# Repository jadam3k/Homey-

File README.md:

# Homey

Homey is a compact home automation controller designed for residential use, while also being capable of operating as an industrial-style PLC for control and monitoring tasks.

The project combines Ethernet connectivity, isolated digital I/O, relay outputs, and flexible power input in a single hardware platform built around ESP32.

---

## Hardware Features

* **ESP32-based architecture** for wireless communication, local control logic, and future expansion.
* **Ethernet with PoE support** for reliable wired connectivity and simplified installation.
* **4 digital inputs** for external sensors, switches, and automation signals.
* **4 digital outputs** based on relays for switching external loads.
* **5 onboard LEDs** used for status indication, diagnostics, and visual feedback.
* **Input voltage up to 24V** for industrial and field applications.
* **5V relay section** powered separately while maintaining compatibility with higher external voltages.
* **USB-C power support** for development, testing, and low-voltage standalone operation.
* **Optocoupler isolation** allowing safe interfacing with higher voltage external circuits.

---

## Electrical Design Notes

The board is divided into functional sections.

High-voltage and switching circuitry are separated from the low-voltage logic domain in order to improve stability, reduce electrical noise, and increase operational safety.

Special attention was given to routing of high-speed and differential signals such as:

* Ethernet TX / RX
* USB D+ / D−

Component placement and routing were performed with signal integrity and practical manufacturability in mind.

---

## Firmware

The firmware has been completed and provides the basic control layer for the board.

The current software handles:

* digital input reading
* relay output control
* status LED logic
* Ethernet communication foundation

The architecture was kept clean and modular to allow future expansion for everyone - you do what you want :).

A future direction of development is communication between multiple boards using **ESP-NOW**, enabling distributed control nodes over larger areas (2/3km).

---

## Project Images

### 3D Model

### Schematic

### PCB Layout / Routed Board

---

## Project Status

The project is currently considered **complete**.

Remember, if you copy it. Mention me :) i will check that.

---

## License
Just do not consider this project as your own :)

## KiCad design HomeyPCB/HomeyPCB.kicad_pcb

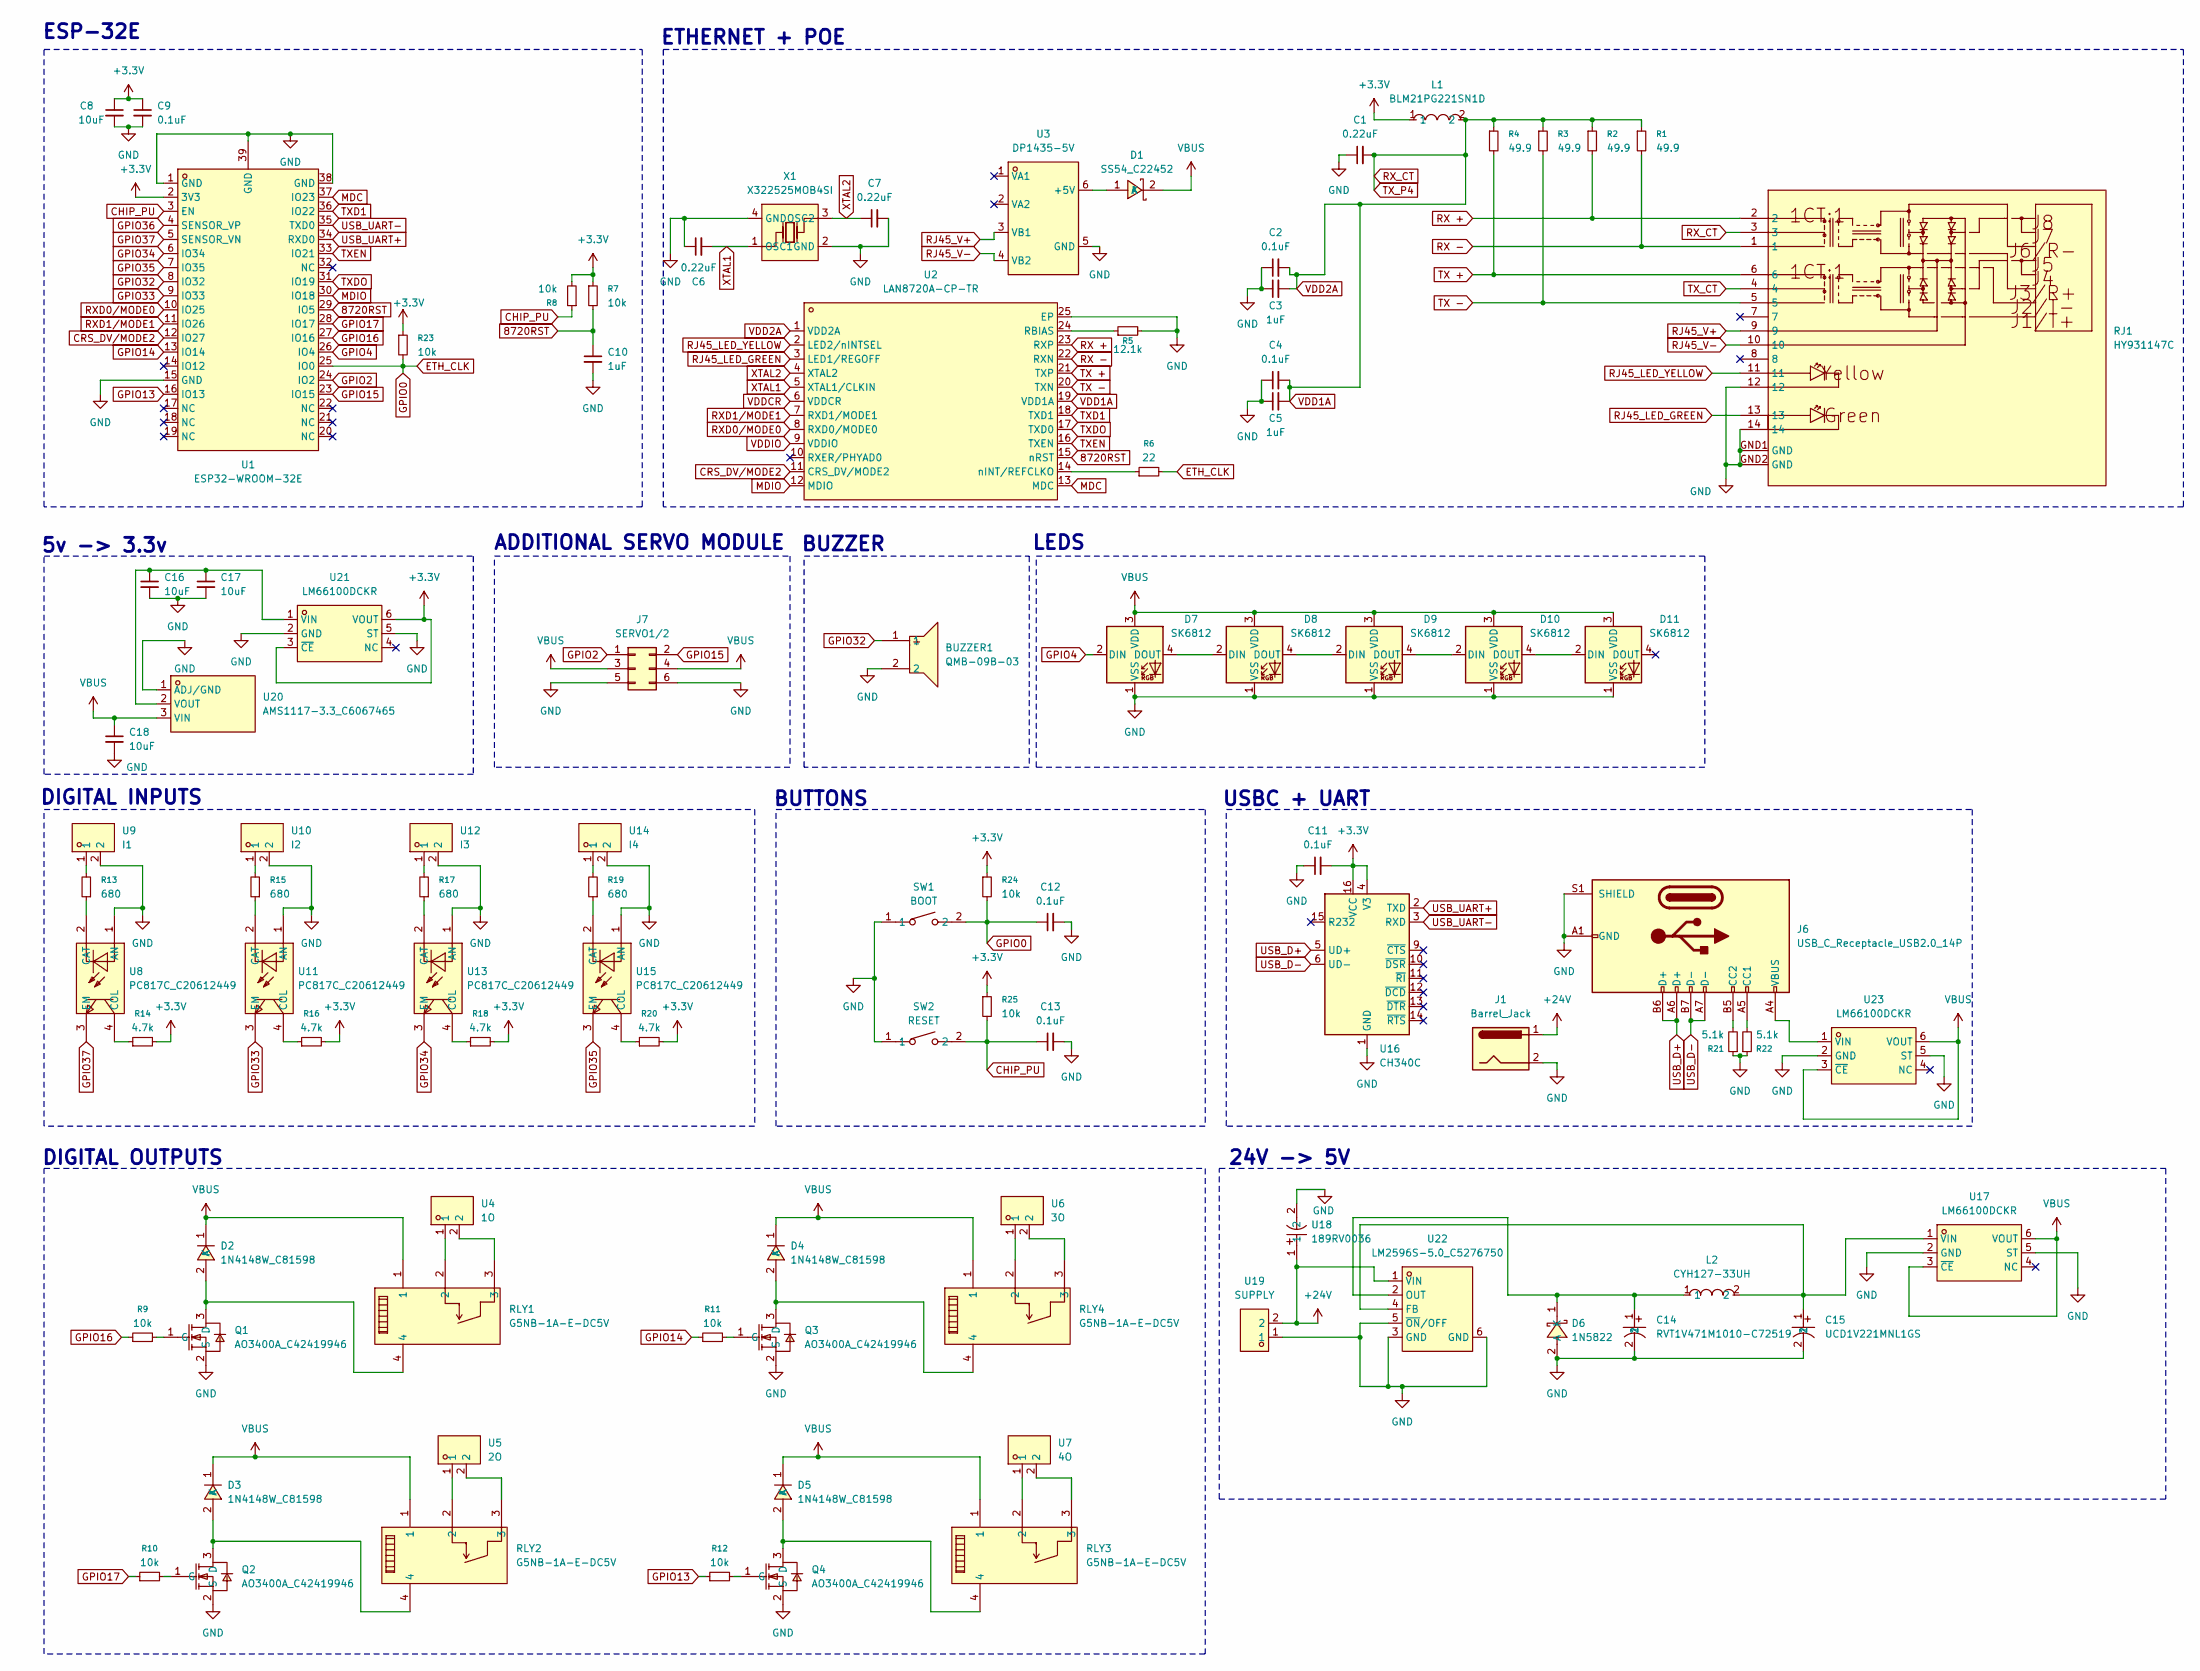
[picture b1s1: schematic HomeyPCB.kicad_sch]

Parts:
BUZZER1: QMB-09B-03; BUZ-TH_BD9.0-P4.00-D0.6-FD; MPN QMB-09B-03; LCSC Part C96256
C1, C6, C7: 0.22uF; C_0603_1608Metric_Pad1.08x0.95mm_HandSolder
C2, C4, C9, C11, C12, C13: 0.1uF; C_0603_1608Metric_Pad1.08x0.95mm_HandSolder
C3, C5, C10: 1uF; C_0603_1608Metric_Pad1.08x0.95mm_HandSolder
C8, C16, C17, C18: 10uF; C_0603_1608Metric_Pad1.08x0.95mm_HandSolder
C14: RVT1V471M1010-C72519; CAP-SMD_BD10.0-L10.3-W10.3-LS11.0-R-RD; MPN RVT1V471M1010; LCSC Part C72519
C15: UCD1V221MNL1GS; CAP-SMD_BD8.0-L8.3-W8.3-LS9.3-FD-2; MPN UCD1V221MNL1GS; LCSC Part C136294
D1: SS54_C22452; SMA_L4.4-W2.8-LS5.4-R-RD; MPN SS54; LCSC Part C22452
D2, D3, D4, D5: 1N4148W_C81598; SOD-123F_L2.7-W1.6-LS3.8-RD; MPN 1N4148W; LCSC Part C81598
D6: 1N5822; DO-201AD_BD5.3-L8.4-P12.50-D1.4-RD; MPN 1N5822; LCSC Part C47345510
D7, D8, D9, D10, D11: SK6812; LED_SK6812_PLCC4_5.0x5.0mm_P3.2mm
J1: Barrel_Jack; BarrelJack_Horizontal
J6: USB_C_Receptacle_USB2.0_14P; USB_C_Receptacle_HRO_TYPE-C-31-M-12
J7: SERVO1/2; PinHeader_2x03_P2.54mm_Vertical
L1: BLM21PG221SN1D; L0805; MPN BLM21PG221SN1D; LCSC Part C85840
L2: CYH127-33UH; IND-SMD_L12.3-W12.3; MPN CYH127-33UH; LCSC Part C2929502
Q1, Q2, Q3, Q4: AO3400A_C42419946; SOT-23-3_L2.9-W1.3-P1.90-LS2.4-BR; MPN AO3400A; LCSC Part C42419946
R1, R2, R3, R4: 49.9; R_0603_1608Metric_Pad0.98x0.95mm_HandSolder
R5: 12.1k; R_0603_1608Metric_Pad0.98x0.95mm_HandSolder
R6: 22; R_0603_1608Metric_Pad0.98x0.95mm_HandSolder
R7, R8, R9, R10, R11, R12, R23, R24, R25: 10k; R_0603_1608Metric_Pad0.98x0.95mm_HandSolder
R13, R15, R17, R19: 680; R_2512_6332Metric_Pad1.40x3.35mm_HandSolder
R14, R16, R18, R20: 4.7k; R_0603_1608Metric_Pad0.98x0.95mm_HandSolder
R21, R22: 5.1k; R_0603_1608Metric_Pad0.98x0.95mm_HandSolder
RJ1: HY931147C; RJ45-TH_HY931147C; MPN HY931147C; LCSC Part C91754
RLY1, RLY2, RLY3, RLY4: G5NB-1A-E-DC5V; RELAY-TH_G5NB-1A-E-DCXX; MPN G5NB-1A-E-DC5V; LCSC Part C48746
SW1: BOOT; SW-SMD_L3.9-W3.0-P4.45; MPN TS-1088-AR02016; LCSC Part C720477
SW2: RESET; SW-SMD_L3.9-W3.0-P4.45; MPN TS-1088-AR02016; LCSC Part C720477
U1: ESP32-WROOM-32E; WIFI-SMD_ESP32-WROOM-32E; MPN ESP32-WROOM-32E-N8; LCSC Part C701342
U2: LAN8720A-CP-TR; QFN-24_L4.0-W4.0-P0.50-BL-EP2.6; MPN LAN8720A-CP-TR; LCSC Part C45223
U3: DP1435-5V; PWRM-TH_L35.6-W16.2-P2.54_DP1435-5V; MPN DP1435-5V; LCSC Part C5380097
U4: 1O; CONN-TH_P5.00_KF301-5.0-2P; MPN KF301-5.0-2P; LCSC Part C474881
U5: 2O; CONN-TH_P5.00_KF301-5.0-2P; MPN KF301-5.0-2P; LCSC Part C474881
U6: 3O; CONN-TH_P5.00_KF301-5.0-2P; MPN KF301-5.0-2P; LCSC Part C474881
U7: 4O; CONN-TH_P5.00_KF301-5.0-2P; MPN KF301-5.0-2P; LCSC Part C474881
U8, U11, U13, U15: PC817C_C20612449; DIP-4_L4.6-W6.5-P2.54-LS7.6-BL; MPN PC817C; LCSC Part C20612449
U9: I1; CONN-TH_P5.00_KF301-5.0-2P; MPN KF301-5.0-2P; LCSC Part C474881
U10: I2; CONN-TH_P5.00_KF301-5.0-2P; MPN KF301-5.0-2P; LCSC Part C474881
U12: I3; CONN-TH_P5.00_KF301-5.0-2P; MPN KF301-5.0-2P; LCSC Part C474881
U14: I4; CONN-TH_P5.00_KF301-5.0-2P; MPN KF301-5.0-2P; LCSC Part C474881
U16: CH340C; SOIC-16_3.9x9.9mm_P1.27mm
U17, U21, U23: LM66100DCKR; SC-70-6_L2.0-W1.3-P0.65-LS2.1-BL; MPN LM66100DCKR; LCSC Part C2869734
U18: 189RV0036; CAP-SMD_BD10.0-L10.3-W10.3-LS10.8-FD; MPN 189RV0036; LCSC Part C7471898
U19: SUPPLY; CONN-TH_P5.00_KF301-5.0-2P; MPN KF301-5.0-2P; LCSC Part C474881
U20: AMS1117-3.3_C6067465; SOT-89-3_L4.5-W2.5-P1.50-LS4.2-BR; MPN AMS1117-3.3; LCSC Part C6067465
U22: LM2596S-5.0_C5276750; TO-263-5_L10.1-W8.7-P1.70-LS15.2-BR; MPN LM2596S-5.0; LCSC Part C5276750
X1: X322525MOB4SI; CRYSTAL-SMD_4P-L3.2-W2.5-BL; MPN X322525MOB4SI; LCSC Part C9006

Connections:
8720RST: C10.1, R7.2, U1.29 (IO5), U2.15 (nRST)
+3.3V: C8.1, C9.1, C11.2, L1.1, R7.1, R8.2, R14.2, R16.2, R18.2, R20.2, R23.1, R24.1, R25.1, U1.2 (3V3), U16.4 (V3), U16.16 (VCC), U21.3 (~CE), U21.6 (VOUT)
+24V: J1.1, U18.1, U19.2, U22.1 (VIN)
CHIP_PU: C13.1, R8.1, R25.2, SW2.2, U1.3 (EN)
CRS_DV/MODE2: U1.12 (IO27), U2.11 (CRS_DV/MODE2)
ETH_CLK: C12.1, R6.2, R23.2, R24.2, SW1.2, U1.25 (IO0)
GND: BUZZER1.2, C1.1, C2.1, C3.1, C4.1, C5.1, C6.1, C7.2, C8.2, C9.2, C10.2, C11.1, C12.2, C13.2, C14.2, C15.2, C16.2, C17.2, C18.2, D6.2 (A), D7.1 (VSS), D8.1 (VSS), D9.1 (VSS), D10.1 (VSS), D11.1 (VSS), J1.2, J6.A1 (GND), J6.A12 (GND), J6.B1 (GND), J6.B12 (GND), J6.S1 (SHIELD), J7.5, J7.6, Q1.2 (S), Q2.2 (S), Q3.2 (S), Q4.2 (S), R5.2, R21.1, R22.1, RJ1.12, RJ1.14, RJ1.GND1 (GND), RJ1.GND2 (GND), SW1.1, SW2.1, U1.1 (GND), U1.15 (GND), U1.38 (GND), U1.39 (GND), U2.25 (EP), U3.5 (GND), U8.1 (AN), U9.2, U10.2, U11.1 (AN), U12.2, U13.1 (AN), U14.2, U15.1 (AN), U16.1 (GND), U17.2 (GND), U17.5 (ST), U18.2, U19.1, U20.1 (ADJ/GND), U21.2 (GND), U21.5 (ST), U22.3 (GND), U22.5 (~ON/OFF), U22.6 (GND), U23.2 (GND), U23.5 (ST), X1.2 (GND), X1.4 (GND)
GPIO2: J7.1, U1.24 (IO2)
GPIO4: D7.2 (DIN), U1.26 (IO4)
GPIO13: R12.1, U1.16 (IO13)
GPIO14: R11.1, U1.13 (IO14)
GPIO15: J7.2, U1.23 (IO15)
GPIO16: R9.1, U1.27 (IO16)
GPIO17: R10.1, U1.28 (IO17)
GPIO32: BUZZER1.1, U1.8 (IO32)
GPIO33: U1.9 (IO33), U11.3 (EM)
GPIO34: U1.6 (IO34), U13.3 (EM)
GPIO35: U1.7 (IO35), U15.3 (EM)
GPIO36: U1.4 (SENSOR_VP)
GPIO37: U1.5 (SENSOR_VN), U8.3 (EM)
MDC: U1.37 (IO23), U2.13 (MDC)
MDIO: U1.30 (IO18), U2.12 (MDIO)
unnamed: D1.1 (A), U3.6 (+5V)
unnamed: D2.2 (A), Q1.3 (D), RLY1.4
unnamed: D3.2 (A), Q2.3 (D), RLY2.4
unnamed: D4.2 (A), Q3.3 (D), RLY4.4
unnamed: D5.2 (A), Q4.3 (D), RLY3.4
unnamed: C14.1, D6.1 (K), L2.1, U22.2 (OUT)
unnamed: D7.4 (DOUT), D8.2 (DIN)
unnamed: D8.4 (DOUT), D9.2 (DIN)
unnamed: D9.4 (DOUT), D10.2 (DIN)
unnamed: D10.4 (DOUT), D11.2 (DIN)
unnamed: J6.A5 (CC1), R22.2
unnamed: J6.B5 (CC2), R21.2
unnamed: Q1.1 (G), R9.2
unnamed: Q2.1 (G), R10.2
unnamed: Q3.1 (G), R11.2
unnamed: Q4.1 (G), R12.2
unnamed: R13.2, U9.1
unnamed: R15.2, U10.1
unnamed: R17.2, U12.1
unnamed: R19.2, U14.1
unnamed: RLY1.2, U4.1
unnamed: RLY1.3, U4.2
unnamed: RLY2.2, U5.1
unnamed: RLY2.3, U5.2
unnamed: RLY3.2, U7.1
unnamed: RLY3.3, U7.2
unnamed: RLY4.2, U6.1
unnamed: RLY4.3, U6.2
unnamed: R5.1, U2.24 (RBIAS)
unnamed: R6.1, U2.14 (nINT/REFCLKO)
unnamed: R13.1, U8.2 (CAT)
unnamed: R14.1, U8.4 (COL)
unnamed: R15.1, U11.2 (CAT)
unnamed: R16.1, U11.4 (COL)
unnamed: R17.1, U13.2 (CAT)
unnamed: R18.1, U13.4 (COL)
unnamed: R19.1, U15.2 (CAT)
unnamed: R20.1, U15.4 (COL)
unnamed: C15.1, L2.2, U17.1 (VIN), U22.4 (FB)
unnamed: C16.1, C17.1, U20.2 (VOUT), U21.1 (VIN)
unnamed: J6.A4 (VBUS), J6.A9 (VBUS), J6.B4 (VBUS), J6.B9 (VBUS), U23.1 (VIN)
RJ45_LED_GREEN: RJ1.13, U2.3 (LED1/REGOFF)
RJ45_LED_YELLOW: RJ1.11, U2.2 (LED2/nINTSEL)
RJ45_V+: RJ1.9, U3.3 (VB1)
RJ45_V-: RJ1.10, U3.4 (VB2)
RX +: R2.2, RJ1.2, U2.23 (RXP)
RX -: R1.2, RJ1.1, U2.22 (RXN)
RXD0/MODE0: U1.10 (IO25), U2.8 (RXD0/MODE0)
RXD1/MODE1: U1.11 (IO26), U2.7 (RXD1/MODE1)
RX_CT: C1.2, C2.2, C3.2, C4.2, C5.2, L1.2, R1.1, R2.1, R3.1, R4.1, RJ1.3, U2.1 (VDD2A), U2.19 (VDD1A)
TX +: R4.2, RJ1.6, U2.21 (TXP)
TX -: R3.2, RJ1.5, U2.20 (TXN)
TXD1: U1.36 (IO22), U2.18 (TXD1)
TXDO: U1.31 (IO19), U2.17 (TXD0)
TXEN: U1.33 (IO21), U2.16 (TXEN)
TX_CT: RJ1.4
USB_D+: J6.A6 (D+), J6.B6 (D+), U16.5 (UD+)
USB_D-: J6.A7 (D-), J6.B7 (D-), U16.6 (UD-)
USB_UART+: U1.34 (RXD0), U16.2 (TXD)
USB_UART-: U1.35 (TXD0), U16.3 (RXD)
VBUS: C18.1, D1.2 (K), D2.1 (K), D3.1 (K), D4.1 (K), D5.1 (K), D7.3 (VDD), D8.3 (VDD), D9.3 (VDD), D10.3 (VDD), D11.3 (VDD), J7.3, J7.4, RLY1.1, RLY2.1, RLY3.1, RLY4.1, U17.3 (~CE), U17.6 (VOUT), U20.3 (VIN), U23.3 (~CE), U23.6 (VOUT)
VDDCR: U2.6 (VDDCR)
VDDIO: U2.9 (VDDIO)
XTAL1: C6.2, U2.5 (XTAL1/CLKIN), X1.1 (OSC1)
XTAL2: C7.1, U2.4 (XTAL2), X1.3 (OSC2)

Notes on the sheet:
ESP-32E
USBC + UART
ETHERNET + POE
5v -> 3.3v
BUTTONS
LEDS
DIGITAL INPUTS
BUZZER
ADDITIONAL SERVO MODULE
24V -> 5V
DIGITAL OUTPUTS

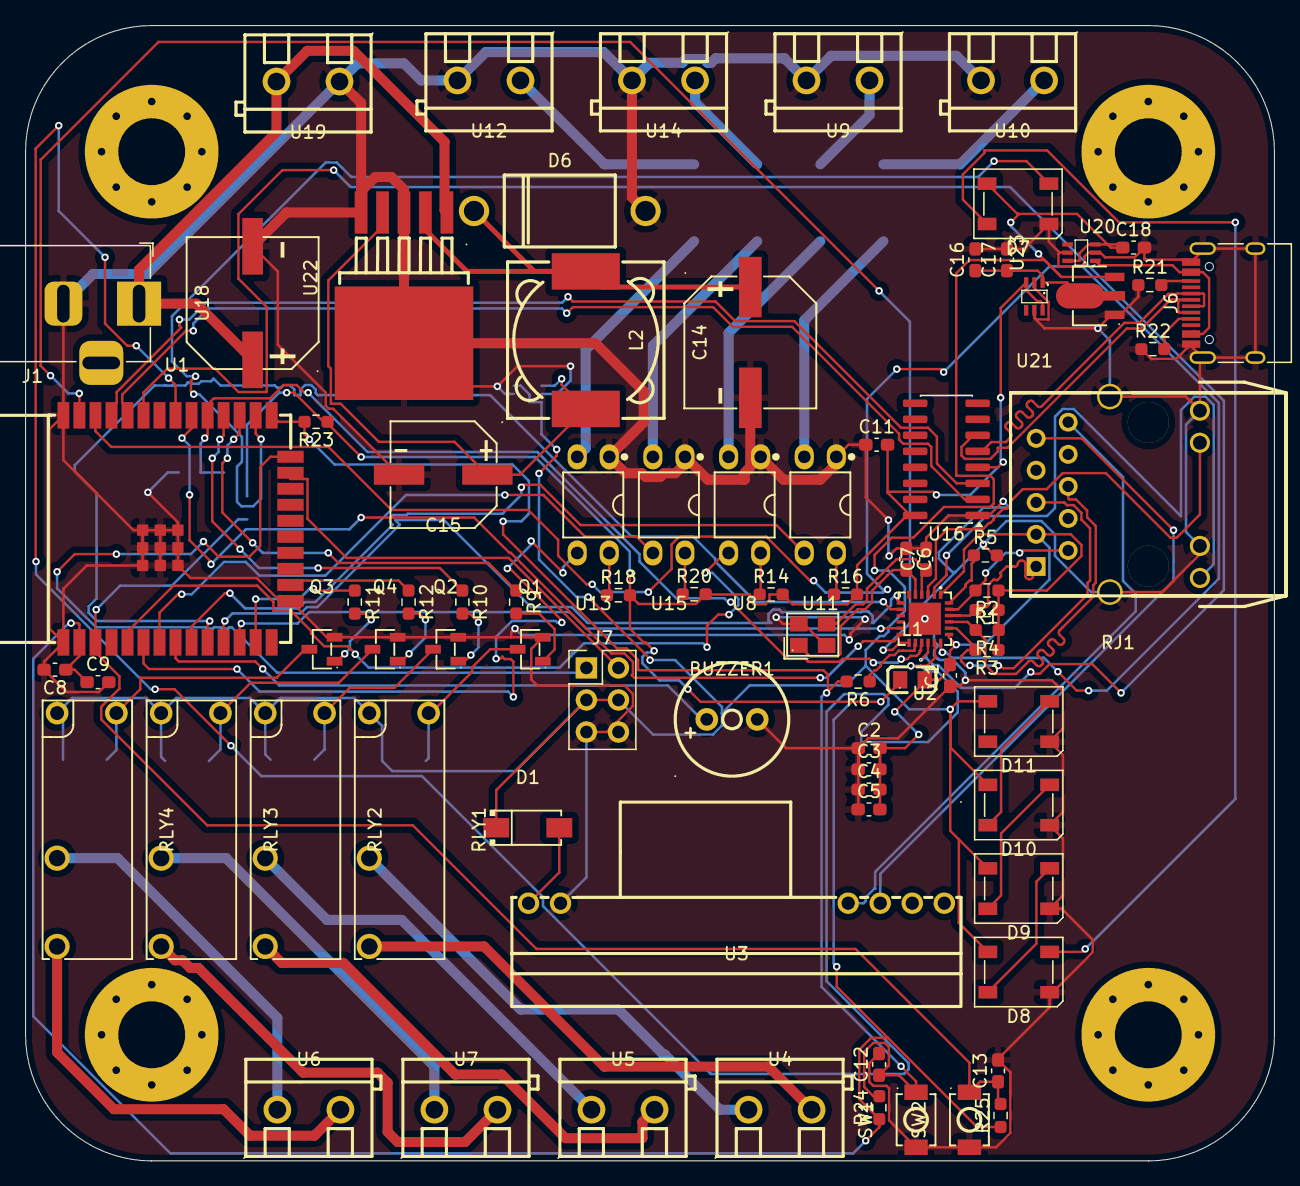
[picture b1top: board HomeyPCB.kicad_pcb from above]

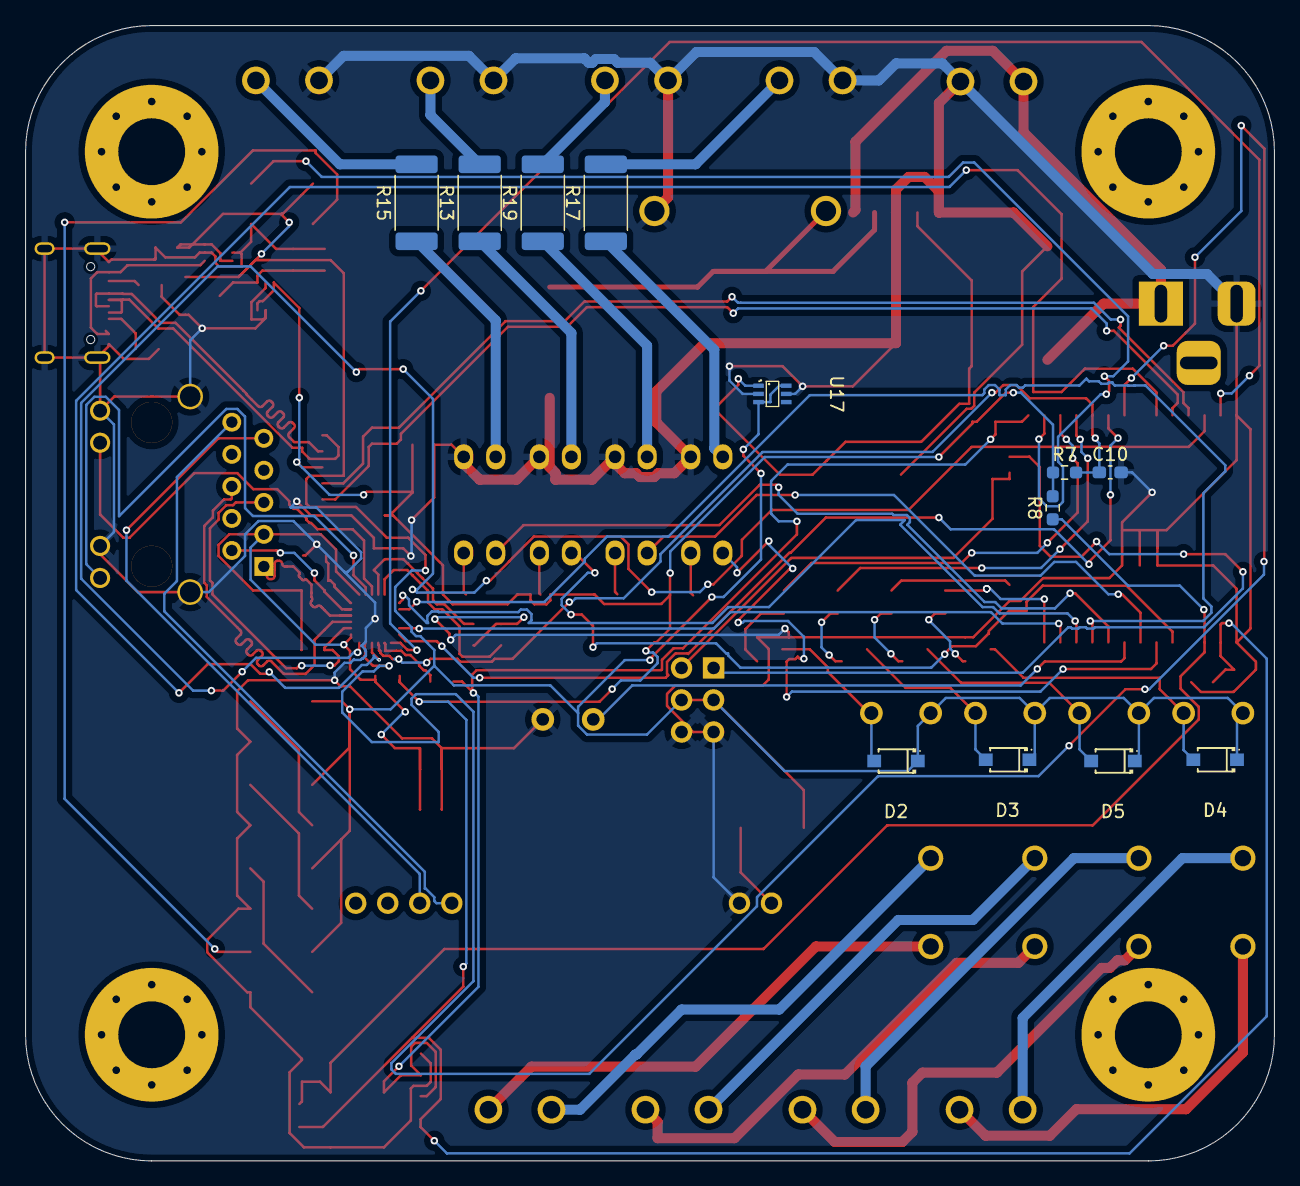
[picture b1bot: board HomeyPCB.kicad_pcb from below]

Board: 2 copper layers, 99.0 x 90.0 mm, 95 parts (12 on the bottom side), 83 nets.

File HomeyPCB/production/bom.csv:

Designator,Footprint,Quantity,Value,LCSC Part #
BUZZER1,BUZ-TH_BD9.0-P4.00-D0.6-FD,1,QMB-09B-03,C96256
"C1, C6, C7",0603,3,0.22uF,
"C10, C3, C5",0603,3,1uF,
"C11, C12, C13, C2, C4, C9",0603,6,0.1uF,
C14,CAP-SMD_BD10.0-L10.3-W10.3-LS11.0-R-RD,1,RVT1V471M1010-C72519,C72519
C15,CAP-SMD_BD8.0-L8.3-W8.3-LS9.3-FD-2,1,UCD1V221MNL1GS,C136294
"C16, C17, C18, C8",0603,4,10uF,
D1,SMA_L4.4-W2.8-LS5.4-R-RD,1,SS54_C22452,C22452
"D10, D11, D7, D8, D9",LED_SK6812_PLCC4_5.0x5.0mm_P3.2mm,5,SK6812,
"D2, D3, D4, D5",SOD-123F_L2.7-W1.6-LS3.8-RD,4,1N4148W_C81598,C81598
D6,DO-201AD_BD5.3-L8.4-P12.50-D1.4-RD,1,1N5822,C47345510
J1,BarrelJack_Horizontal,1,Barrel_Jack,
J6,USB_C_Receptacle_HRO_TYPE-C-31-M-12,1,USB_C_Receptacle_USB2.0_14P,
J7,PinHeader_2x03_P2.54mm_Vertical,1,SERVO1/2,
L1,L0805,1,BLM21PG221SN1D,C85840
L2,IND-SMD_L12.3-W12.3,1,CYH127-33UH,C2929502
"Q1, Q2, Q3, Q4",SOT-23-3_L2.9-W1.3-P1.90-LS2.4-BR,4,AO3400A_C42419946,C42419946
"R1, R2, R3, R4",0603,4,49.9,
"R10, R11, R12, R23, R24, R25, R7, R8, R9",0603,9,10k,
"R13, R15, R17, R19",2512,4,680,
"R14, R16, R18, R20",0603,4,4.7k,
"R21, R22",0603,2,5.1k,
R5,0603,1,12.1k,
R6,0603,1,22,
RJ1,RJ45-TH_HY931147C,1,HY931147C,C91754
"RLY1, RLY2, RLY3, RLY4",RELAY-TH_G5NB-1A-E-DCXX,4,G5NB-1A-E-DC5V,C48746
SW1,SW-SMD_L3.9-W3.0-P4.45,1,BOOT,C720477
SW2,SW-SMD_L3.9-W3.0-P4.45,1,RESET,C720477
U1,WIFI-SMD_ESP32-WROOM-32E,1,ESP32-WROOM-32E,C701342
U10,CONN-TH_P5.00_KF301-5.0-2P,1,I2,C474881
"U11, U13, U15, U8",DIP-4_L4.6-W6.5-P2.54-LS7.6-BL,4,PC817C_C20612449,C20612449
U12,CONN-TH_P5.00_KF301-5.0-2P,1,I3,C474881
U14,CONN-TH_P5.00_KF301-5.0-2P,1,I4,C474881
U16,SOIC-16_3.9x9.9mm_P1.27mm,1,CH340C,
"U17, U21, U23",SC-70-6_L2.0-W1.3-P0.65-LS2.1-BL,3,LM66100DCKR,C2869734
U18,CAP-SMD_BD10.0-L10.3-W10.3-LS10.8-FD,1,189RV0036,C7471898
U19,CONN-TH_P5.00_KF301-5.0-2P,1,SUPPLY,C474881
U2,QFN-24_L4.0-W4.0-P0.50-BL-EP2.6,1,LAN8720A-CP-TR,C45223
U20,SOT-89-3_L4.5-W2.5-P1.50-LS4.2-BR,1,AMS1117-3.3_C6067465,C6067465
U22,TO-263-5_L10.1-W8.7-P1.70-LS15.2-BR,1,LM2596S-5.0_C5276750,C5276750
U3,PWRM-TH_L35.6-W16.2-P2.54_DP1435-5V,1,DP1435-5V,C5380097
U4,CONN-TH_P5.00_KF301-5.0-2P,1,1O,C474881
U5,CONN-TH_P5.00_KF301-5.0-2P,1,2O,C474881
U6,CONN-TH_P5.00_KF301-5.0-2P,1,3O,C474881
U7,CONN-TH_P5.00_KF301-5.0-2P,1,4O,C474881
U9,CONN-TH_P5.00_KF301-5.0-2P,1,I1,C474881
X1,CRYSTAL-SMD_4P-L3.2-W2.5-BL,1,X322525MOB4SI,C9006
